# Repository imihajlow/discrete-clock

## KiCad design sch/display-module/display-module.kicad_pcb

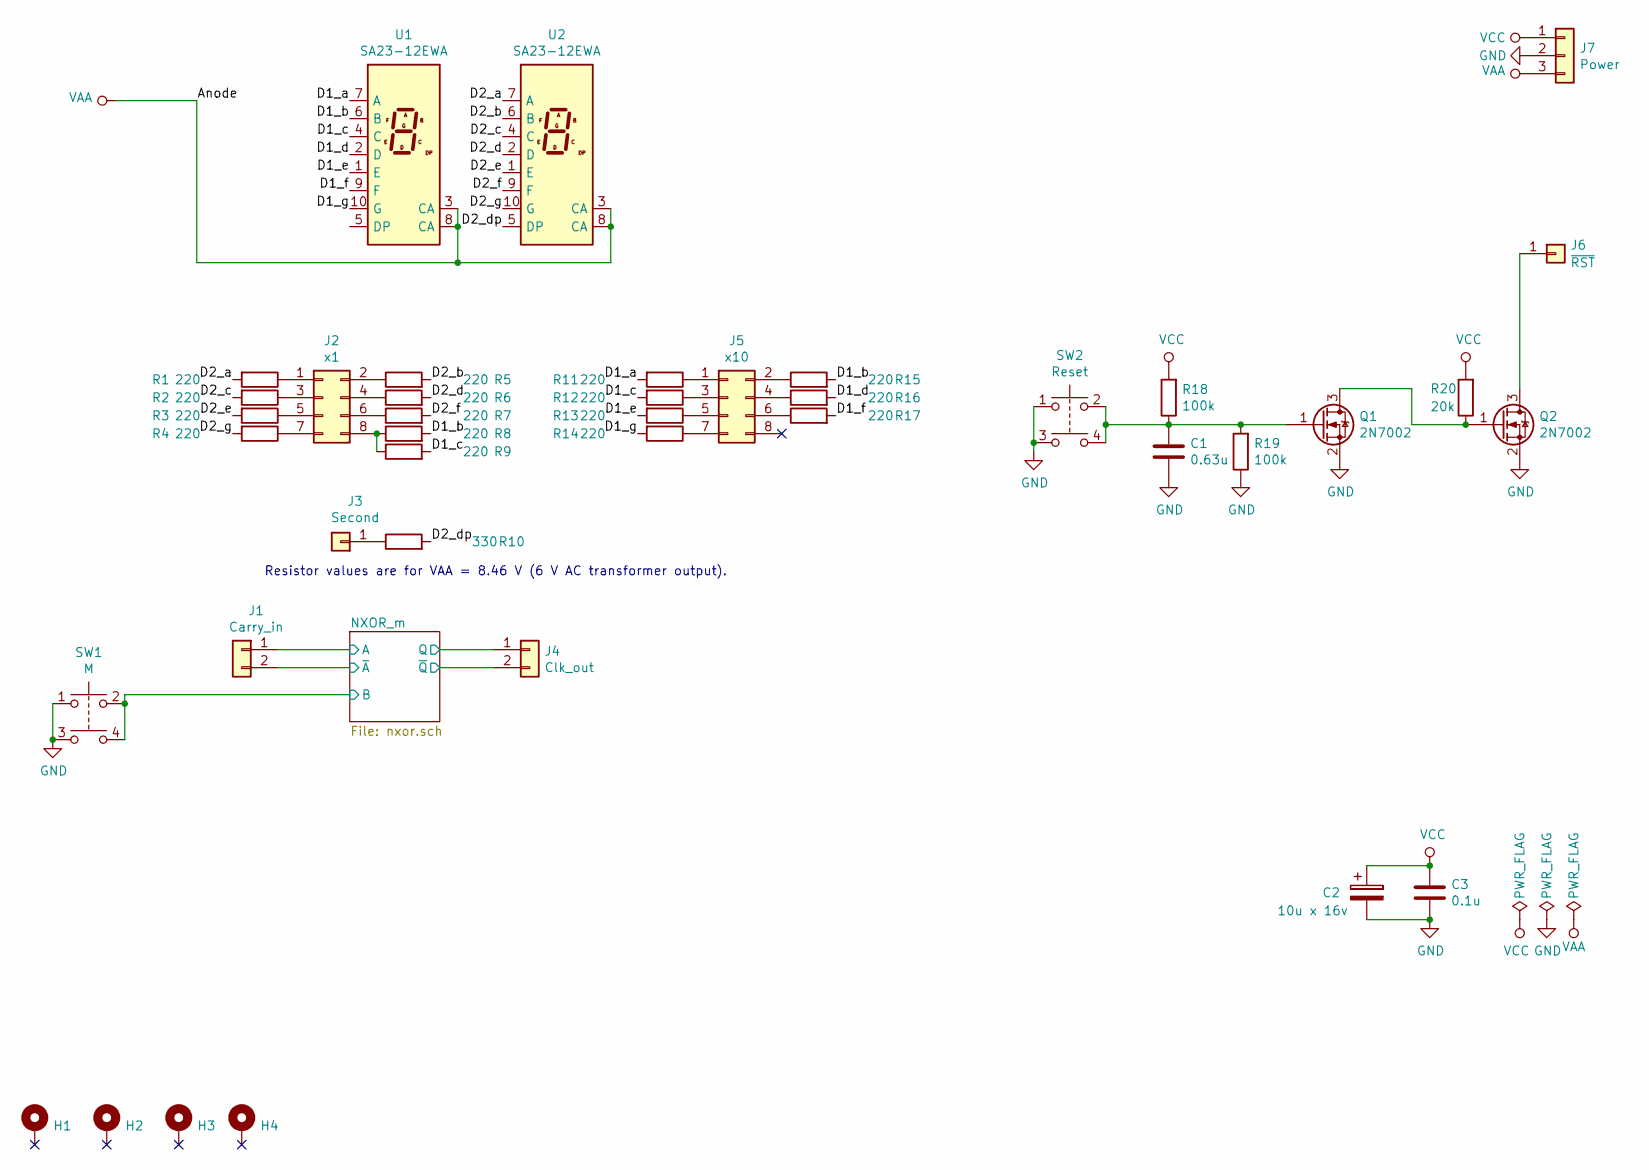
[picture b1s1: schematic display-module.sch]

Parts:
C1: 0.63u; C_0805_2012Metric
C2: 10u x 16v; CP_EIA-3528-21_Kemet-B_Pad1.50x2.35mm_HandSolder
C3: 0.1u; C_0805_2012Metric
H1, H2, H3, H4: MountingHole_Pad; MountingHole_3.2mm_M3_DIN965_Pad
J1: Carry_in; PinHeader_1x02_P2.54mm_Vertical
J2: x1; IDC-Header_2x04_P2.54mm_Vertical
J3: Second; PinHeader_1x01_P2.54mm_Vertical
J4: Clk_out; PinHeader_1x02_P2.54mm_Vertical
J5: x10; IDC-Header_2x04_P2.54mm_Vertical
J6: ~RST; PinHeader_1x01_P2.54mm_Vertical
J7: Power; PinHeader_1x03_P2.54mm_Vertical
Q1, Q2: 2N7002; SOT-23
R1, R2, R3, R4, R5, R6, R7, R8, R9, R11, R12, R13, R14, R15, R16, R17: 220; R_0805_2012Metric
R10: 330; R_0805_2012Metric
R18, R19: 100k; R_0805_2012Metric
R20: 20k; R_0805_2012Metric
SW1: M; DTS-644
SW2: Reset; DTS-644
U1, U2: SA23-12EWA; SA10-21HWA

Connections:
/D1_a: R11.2, U1.7 (A)
/D1_b: R8.2, R15.2, U1.6 (B)
/D1_c: R9.2, R12.2, U1.4 (C)
/D1_d: R16.2, U1.2 (D)
/D1_e: R13.2, U1.1 (E)
/D1_f: R17.2, U1.9 (F)
/D1_g: R14.2, U1.10 (G)
/D2_a: R1.2, U2.7 (A)
/D2_b: R5.2, U2.6 (B)
/D2_c: R2.2, U2.4 (C)
/D2_d: R6.2, U2.2 (D)
/D2_dp: R10.2, U2.5 (DP)
/D2_e: R3.2, U2.1 (E)
/D2_f: R7.2, U2.9 (F)
/D2_g: R4.2, U2.10 (G)
/NXOR_m/A: J1.1; also elsewhere on the board
/NXOR_m/B: SW1.2, SW1.4; also elsewhere on the board
/NXOR_m/Q: J4.1; also elsewhere on the board
/NXOR_m/~A: J1.2; also elsewhere on the board
/NXOR_m/~Q: J4.2; also elsewhere on the board
GND: C1.2, C2.2, C3.2, J7.2, Q1.2 (S), Q2.2 (S), R19.1, SW1.1, SW1.3, SW2.1, SW2.3; also elsewhere on the board
unnamed: C1.1, Q1.1 (G), R18.1, R19.2, SW2.2, SW2.4
unnamed: J2.1, R1.1
unnamed: J2.2, R5.1
unnamed: J2.3, R2.1
unnamed: J2.4, R6.1
unnamed: J2.5, R3.1
unnamed: J2.6, R7.1
unnamed: J2.7, R4.1
unnamed: J2.8, R8.1, R9.1
unnamed: J3.1, R10.1
unnamed: J5.1, R11.1
unnamed: J5.2, R15.1
unnamed: J5.3, R12.1
unnamed: J5.4, R16.1
unnamed: J5.5, R13.1
unnamed: J5.6, R17.1
unnamed: J5.7, R14.1
unnamed: J6.1, Q2.3 (D)
unnamed: Q1.3 (D), Q2.1 (G), R20.1
VAA: J7.3, U1.3 (CA), U1.8 (CA), U2.3 (CA), U2.8 (CA)
VCC: C2.1, C3.1, J7.1, R18.2, R20.2; also elsewhere on the board

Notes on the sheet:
Resistor values are for VAA = 8.46 V (6 V AC transformer output).

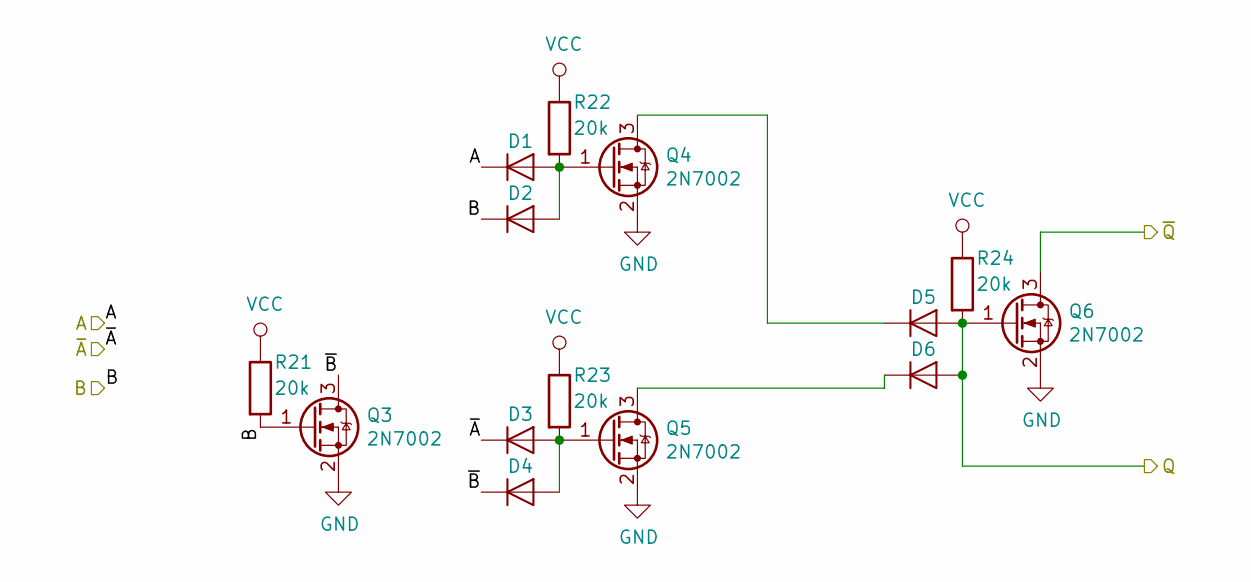
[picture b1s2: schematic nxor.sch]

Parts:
D1, D2, D3, D4, D5, D6: LL103C; D_MiniMELF
Q3, Q4, Q5, Q6: 2N7002; SOT-23
R21, R22, R23, R24: 20k; R_0805_2012Metric

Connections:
/NXOR_m/A: D1.1 (K); also elsewhere on the board
/NXOR_m/B: D2.1 (K), Q3.1 (G), R21.2; also elsewhere on the board
/NXOR_m/Q: D5.2 (A), D6.2 (A), Q6.1 (G), R24.2; also elsewhere on the board
/NXOR_m/~A: D3.1 (K); also elsewhere on the board
/NXOR_m/~B: D4.1 (K), Q3.3 (D)
/NXOR_m/~Q: Q6.3 (D); also elsewhere on the board
GND: Q3.2 (S), Q4.2 (S), Q5.2 (S), Q6.2 (S); also elsewhere on the board
unnamed: D1.2 (A), D2.2 (A), Q4.1 (G), R22.2
unnamed: D3.2 (A), D4.2 (A), Q5.1 (G), R23.2
unnamed: D5.1 (K), Q4.3 (D)
unnamed: D6.1 (K), Q5.3 (D)
VCC: R21.1, R22.1, R23.1, R24.1; also elsewhere on the board

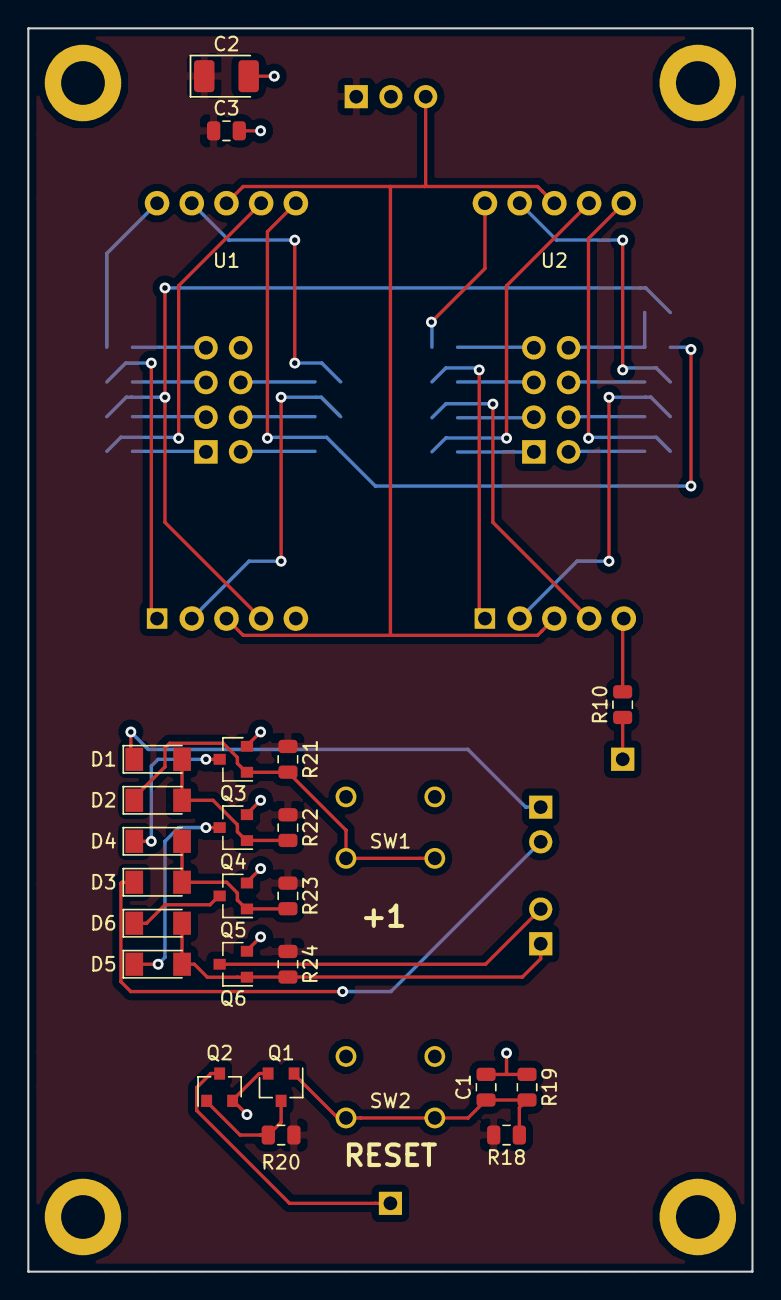
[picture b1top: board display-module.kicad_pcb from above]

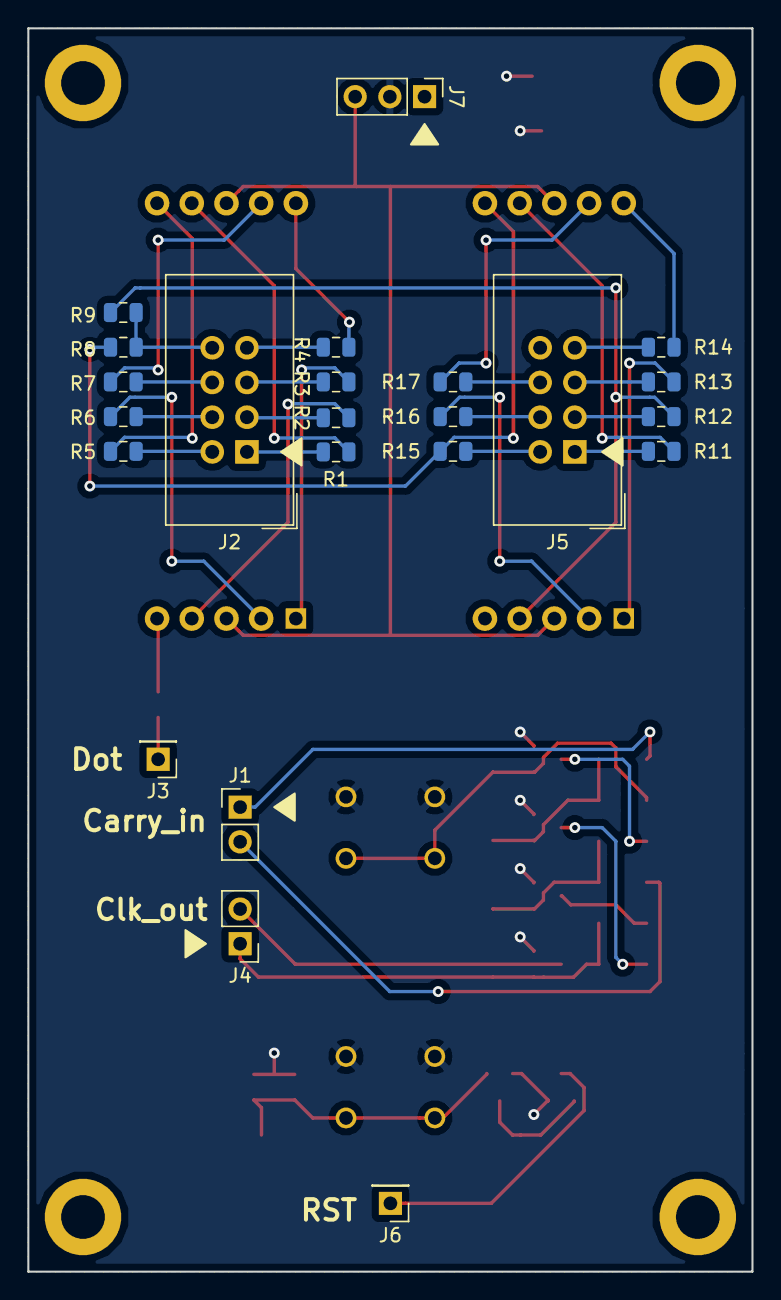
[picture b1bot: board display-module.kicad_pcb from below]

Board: 2 copper layers, 53.0 x 91.0 mm, 54 parts (23 on the bottom side), 47 nets.

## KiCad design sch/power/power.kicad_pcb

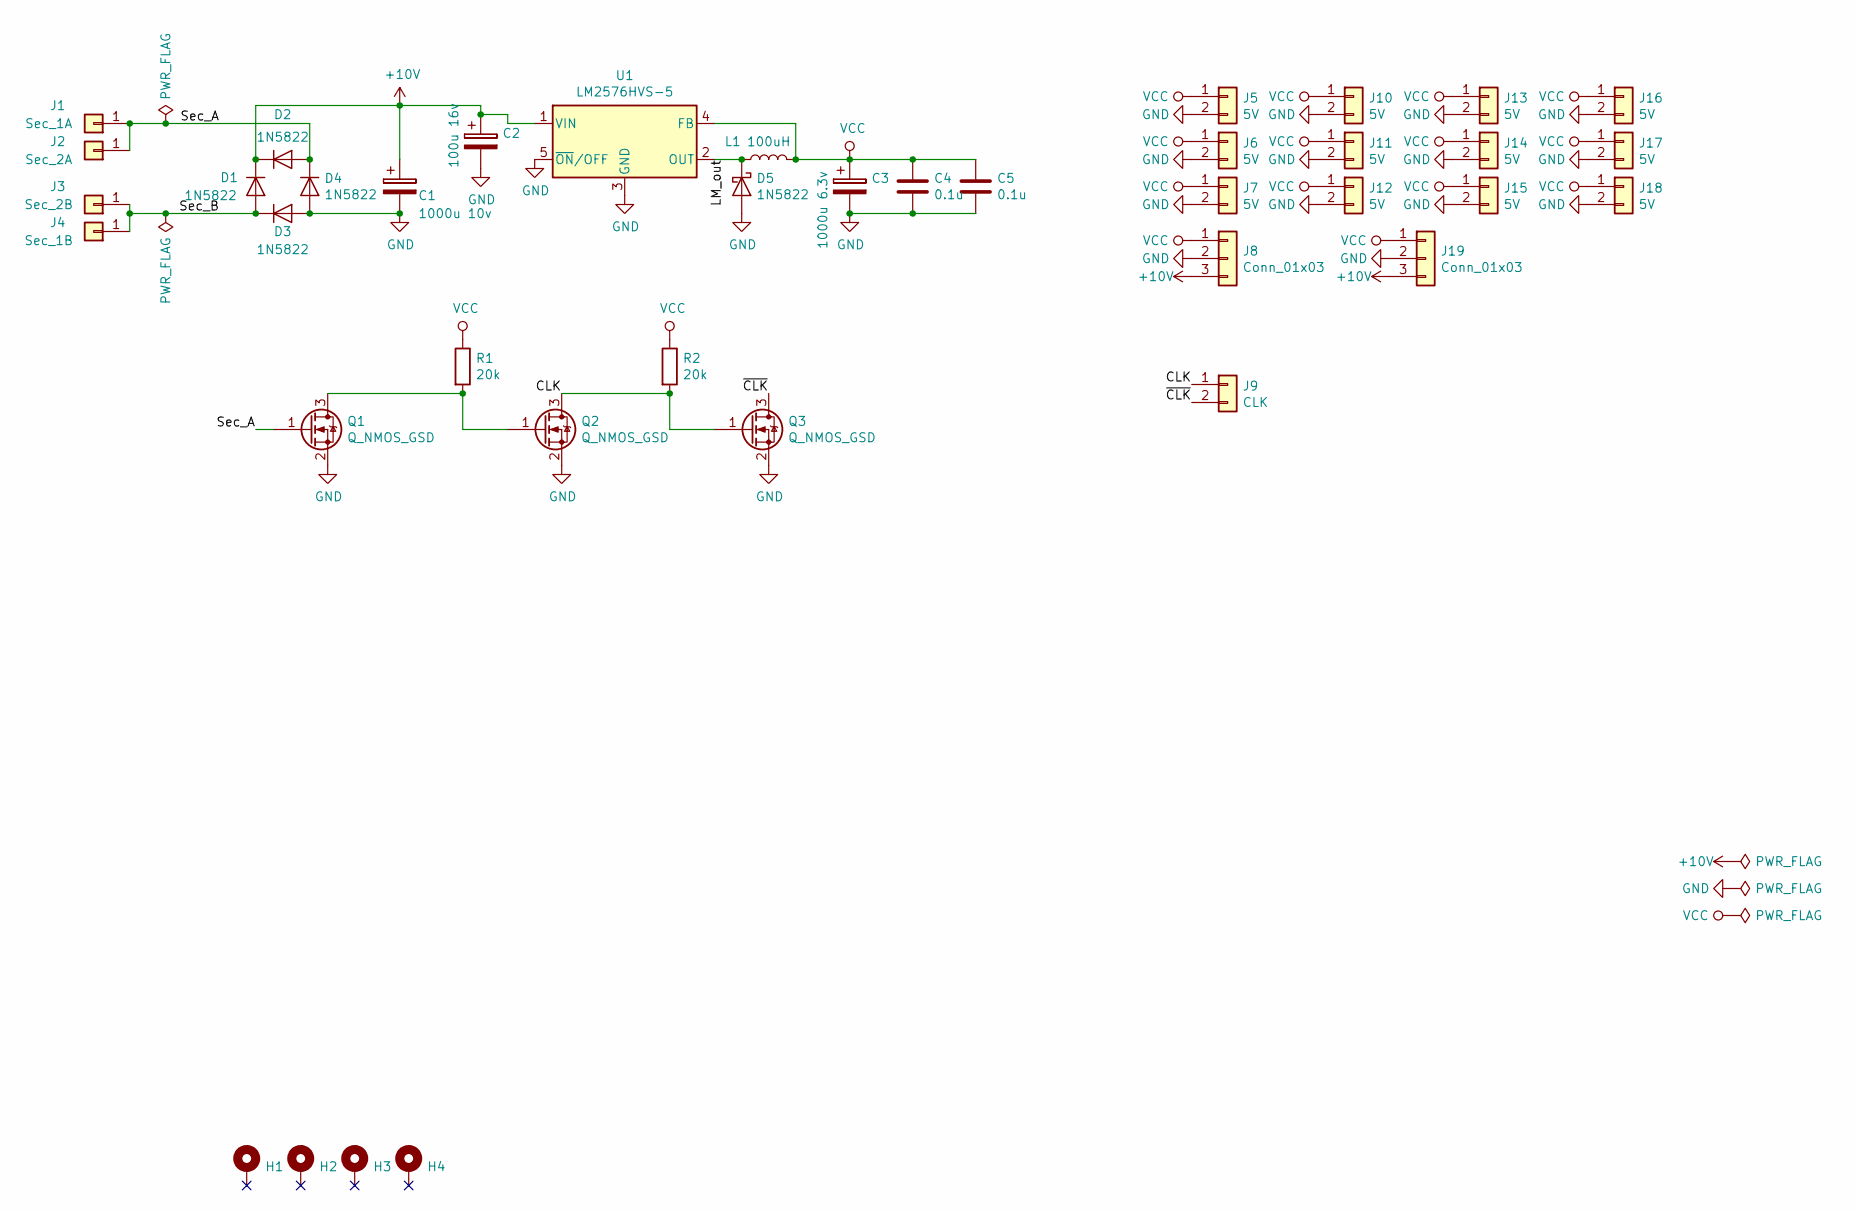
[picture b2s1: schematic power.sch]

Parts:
C1: 1000u 10v; CP_Elec_10x10
C2: 100u 16v; CP_Elec_6.3x5.4
C3: 1000u 6.3v; CP_Elec_8x10.5
C4, C5: 0.1u; C_0805_2012Metric
D1, D2, D3, D4, D5: 1N5822; D_DO-201AD_P12.70mm_Horizontal
H1, H2, H3, H4: MountingHole_Pad; MountingHole_3.2mm_M3_DIN965_Pad
J1: Sec_1A; SolderWirePad_1x01_Drill1.5mm
J2: Sec_2A; SolderWirePad_1x01_Drill1.5mm
J3: Sec_2B; SolderWirePad_1x01_Drill1.5mm
J4: Sec_1B; SolderWirePad_1x01_Drill1.5mm
J5, J6, J7, J10, J11, J12, J13, J14, J15, J16, J17, J18: 5V; PinHeader_1x02_P2.54mm_Vertical
J8, J19: Conn_01x03; PinHeader_1x03_P2.54mm_Vertical
J9: CLK; PinHeader_1x02_P2.54mm_Vertical
L1: 100uH; L_Wuerth_WE-PD-Typ-LS_Handsoldering
Q1, Q2, Q3: Q_NMOS_GSD; SOT-23
R1, R2: 20k; R_0805_2012Metric
U1: LM2576HVS-5; TO-263-5_TabPin3

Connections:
+10V: C1.1, C2.1, D1.1 (K), D2.1 (K), J8.3, J19.3, U1.1 (VIN)
/CLK: J9.1, Q2.3 (D), Q3.1 (G), R2.2
/LM_out: D5.1 (K), L1.1, U1.2 (OUT)
/Sec_A: D2.2 (A), D4.1 (K), J1.1, J2.1, Q1.1 (G)
/Sec_B: D1.2 (A), D3.1 (K), J3.1, J4.1
/~CLK: J9.2, Q3.3 (D)
GND: C1.2, C2.2, C3.2, C4.2, C5.2, D3.2 (A), D4.2 (A), D5.2 (A), J5.2, J6.2, J7.2, J8.2, J10.2, J11.2, J12.2, J13.2, J14.2, J15.2, J16.2, J17.2, J18.2, J19.2, Q1.2 (S), Q2.2 (S), Q3.2 (S), U1.3 (GND), U1.5 (~ON~/OFF)
unnamed: Q1.3 (D), Q2.1 (G), R1.2
VCC: C3.1, C4.1, C5.1, J5.1, J6.1, J7.1, J8.1, J10.1, J11.1, J12.1, J13.1, J14.1, J15.1, J16.1, J17.1, J18.1, J19.1, L1.2, R1.1, R2.1, U1.4 (FB)

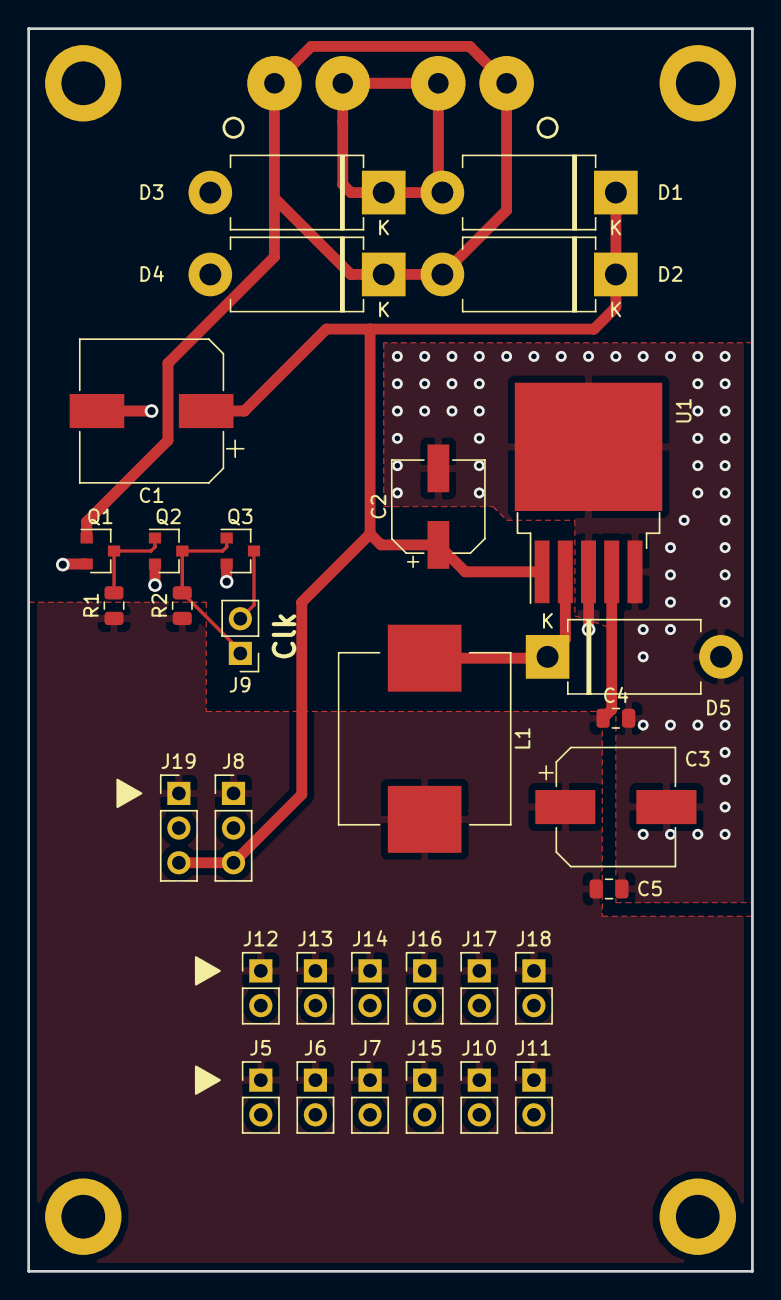
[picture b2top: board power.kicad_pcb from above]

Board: 2 copper layers, 53.0 x 91.0 mm, 40 parts (0 on the bottom side), 9 nets.

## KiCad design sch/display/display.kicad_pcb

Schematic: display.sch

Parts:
C1: 0.63u; C_0805_2012Metric
C2: 10u x 16v; CP_EIA-3528-21_Kemet-B_Pad1.50x2.35mm_HandSolder
C3: 0.1u; C_0805_2012Metric
H1, H2, H3, H4, H5, H6, H7, H8: MountingHole_Pad; MountingHole_3.2mm_M3_DIN965_Pad
J1: S_Carry; PinHeader_1x02_P2.54mm_Vertical
J2: M_Carry; PinHeader_1x02_P2.54mm_Vertical
J3: Hour; IDC-Header_2x04_P2.54mm_Vertical
J4: Second; PinHeader_1x01_P2.54mm_Vertical
J5: M_CLK; PinHeader_1x02_P2.54mm_Vertical
J6: H_CLK; PinHeader_1x02_P2.54mm_Vertical
J7: Minute10; IDC-Header_2x04_P2.54mm_Vertical
J8: Minute1; IDC-Header_2x04_P2.54mm_Vertical
J9: ~RST; PinHeader_1x01_P2.54mm_Vertical
J10: Power; PinHeader_1x03_P2.54mm_Vertical
Q1, Q2: 2N7002; SOT-23
R1, R2, R3, R4, R5, R6, R7, R8, R9, R11, R12, R13, R14, R15, R16, R17, R18, R19, R20, R21, R22, R23, R24: 15; R_0805_2012Metric
R10: 270; R_0805_2012Metric
R25, R26: 100k; R_0805_2012Metric
R27: 20k; R_0805_2012Metric
SW1: M; DTS-644
SW2: H; DTS-644
SW3: Reset; DTS-644
U1, U2, U3, U4: SA23-12EWA; SA10-21HWA

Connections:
/D1_b: R8.2, U1.6 (B)
/D1_c: R9.2, U1.4 (C)
/D2_a: R1.2, U2.7 (A)
/D2_b: R5.2, U2.6 (B)
/D2_c: R2.2, U2.4 (C)
/D2_d: R6.2, U2.2 (D)
/D2_dp: R10.2, U2.5 (DP)
/D2_e: R3.2, U2.1 (E)
/D2_f: R7.2, U2.9 (F)
/D2_g: R4.2, U2.10 (G)
/D3_a: R11.2, U3.7 (A)
/D3_b: R19.2, U3.6 (B)
/D3_c: R12.2, U3.4 (C)
/D3_d: R20.2, U3.2 (D)
/D3_e: R13.2, U3.1 (E)
/D3_f: R21.2, U3.9 (F)
/D3_g: R14.2, U3.10 (G)
/D4_a: R15.2, U4.7 (A)
/D4_b: R22.2, U4.6 (B)
/D4_c: R16.2, U4.4 (C)
/D4_d: R23.2, U4.2 (D)
/D4_e: R17.2, U4.1 (E)
/D4_f: R24.2, U4.9 (F)
/D4_g: R18.2, U4.10 (G)
/NXOR_h/A: J2.1; also elsewhere on the board
/NXOR_h/B: SW2.2, SW2.4; also elsewhere on the board
/NXOR_h/Q: J6.1; also elsewhere on the board
/NXOR_h/~A: J2.2; also elsewhere on the board
/NXOR_h/~Q: J6.2; also elsewhere on the board
/NXOR_m/A: J1.1; also elsewhere on the board
/NXOR_m/B: SW1.2, SW1.4; also elsewhere on the board
/NXOR_m/Q: J5.1; also elsewhere on the board
/NXOR_m/~A: J1.2; also elsewhere on the board
/NXOR_m/~Q: J5.2; also elsewhere on the board
GND: C1.2, C2.2, C3.2, J10.2, Q1.2 (S), Q2.2 (S), R26.1, SW1.1, SW1.3, SW2.1, SW2.3, SW3.1, SW3.3; also elsewhere on the board
unnamed: C1.1, Q1.1 (G), R25.1, R26.2, SW3.2, SW3.4
unnamed: J3.1, R1.1
unnamed: J3.2, R5.1
unnamed: J3.3, R2.1
unnamed: J3.4, R6.1
unnamed: J3.5, R3.1
unnamed: J3.6, R7.1
unnamed: J3.7, R4.1
unnamed: J3.8, R8.1, R9.1
unnamed: J4.1, R10.1
unnamed: J7.1, R11.1
unnamed: J7.2, R19.1
unnamed: J7.3, R12.1
unnamed: J7.4, R20.1
unnamed: J7.5, R13.1
unnamed: J7.6, R21.1
unnamed: J7.7, R14.1
unnamed: J8.1, R15.1
unnamed: J8.2, R22.1
unnamed: J8.3, R16.1
unnamed: J8.4, R23.1
unnamed: J8.5, R17.1
unnamed: J8.6, R24.1
unnamed: J8.7, R18.1
unnamed: J9.1, Q2.3 (D)
unnamed: Q1.3 (D), Q2.1 (G), R27.1
VAA: J10.3, U1.3 (CA), U1.8 (CA), U2.3 (CA), U2.8 (CA), U3.3 (CA), U3.8 (CA), U4.3 (CA), U4.8 (CA)
VCC: C2.1, C3.1, J10.1, R25.2, R27.2; also elsewhere on the board

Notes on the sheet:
Resistor values are for VAA = 8.46 V (6 V AC transformer output).

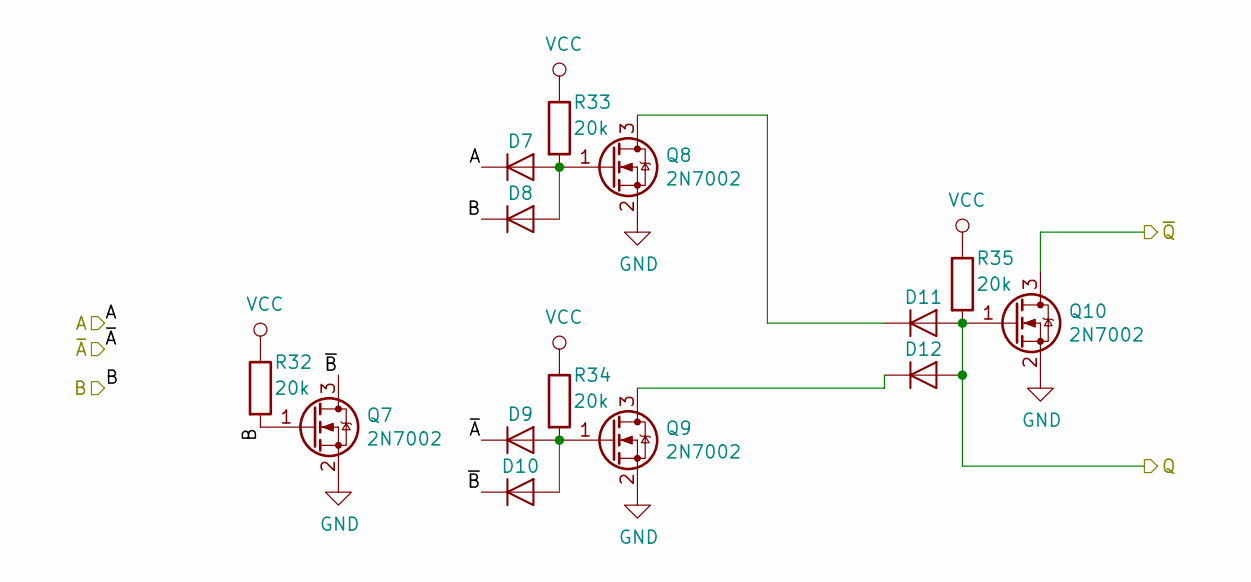
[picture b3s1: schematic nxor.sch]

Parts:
D1, D2, D3, D4, D5, D6: LL103C; D_MiniMELF
Q3, Q4, Q5, Q6: 2N7002; SOT-23
R28, R29, R30, R31: 20k; R_0805_2012Metric

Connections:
/NXOR_m/A: D1.1 (K); also elsewhere on the board
/NXOR_m/B: D2.1 (K), Q3.1 (G), R28.2; also elsewhere on the board
/NXOR_m/Q: D5.2 (A), D6.2 (A), Q6.1 (G), R31.2; also elsewhere on the board
/NXOR_m/~A: D3.1 (K); also elsewhere on the board
/NXOR_m/~B: D4.1 (K), Q3.3 (D)
/NXOR_m/~Q: Q6.3 (D); also elsewhere on the board
GND: Q3.2 (S), Q4.2 (S), Q5.2 (S), Q6.2 (S); also elsewhere on the board
unnamed: D1.2 (A), D2.2 (A), Q4.1 (G), R29.2
unnamed: D3.2 (A), D4.2 (A), Q5.1 (G), R30.2
unnamed: D5.1 (K), Q4.3 (D)
unnamed: D6.1 (K), Q5.3 (D)
VCC: R28.1, R29.1, R30.1, R31.1; also elsewhere on the board

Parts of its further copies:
D7, D8, D9, D10, D11, D12: LL103C; D_MiniMELF
Q7, Q8, Q9, Q10: 2N7002; SOT-23
R32, R33, R34, R35: 20k; R_0805_2012Metric

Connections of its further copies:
/NXOR_h/A: D7.1 (K); also elsewhere on the board
/NXOR_h/B: D8.1 (K), Q7.1 (G), R32.2; also elsewhere on the board
/NXOR_h/Q: D11.2 (A), D12.2 (A), Q10.1 (G), R35.2; also elsewhere on the board
/NXOR_h/~A: D9.1 (K); also elsewhere on the board
/NXOR_h/~B: D10.1 (K), Q7.3 (D)
/NXOR_h/~Q: Q10.3 (D); also elsewhere on the board
GND: Q7.2 (S), Q8.2 (S), Q9.2 (S), Q10.2 (S); also elsewhere on the board
unnamed: D7.2 (A), D8.2 (A), Q8.1 (G), R33.2
unnamed: D9.2 (A), D10.2 (A), Q9.1 (G), R34.2
unnamed: D11.1 (K), Q8.3 (D)
unnamed: D12.1 (K), Q9.3 (D)
VCC: R32.1, R33.1, R34.1, R35.1; also elsewhere on the board

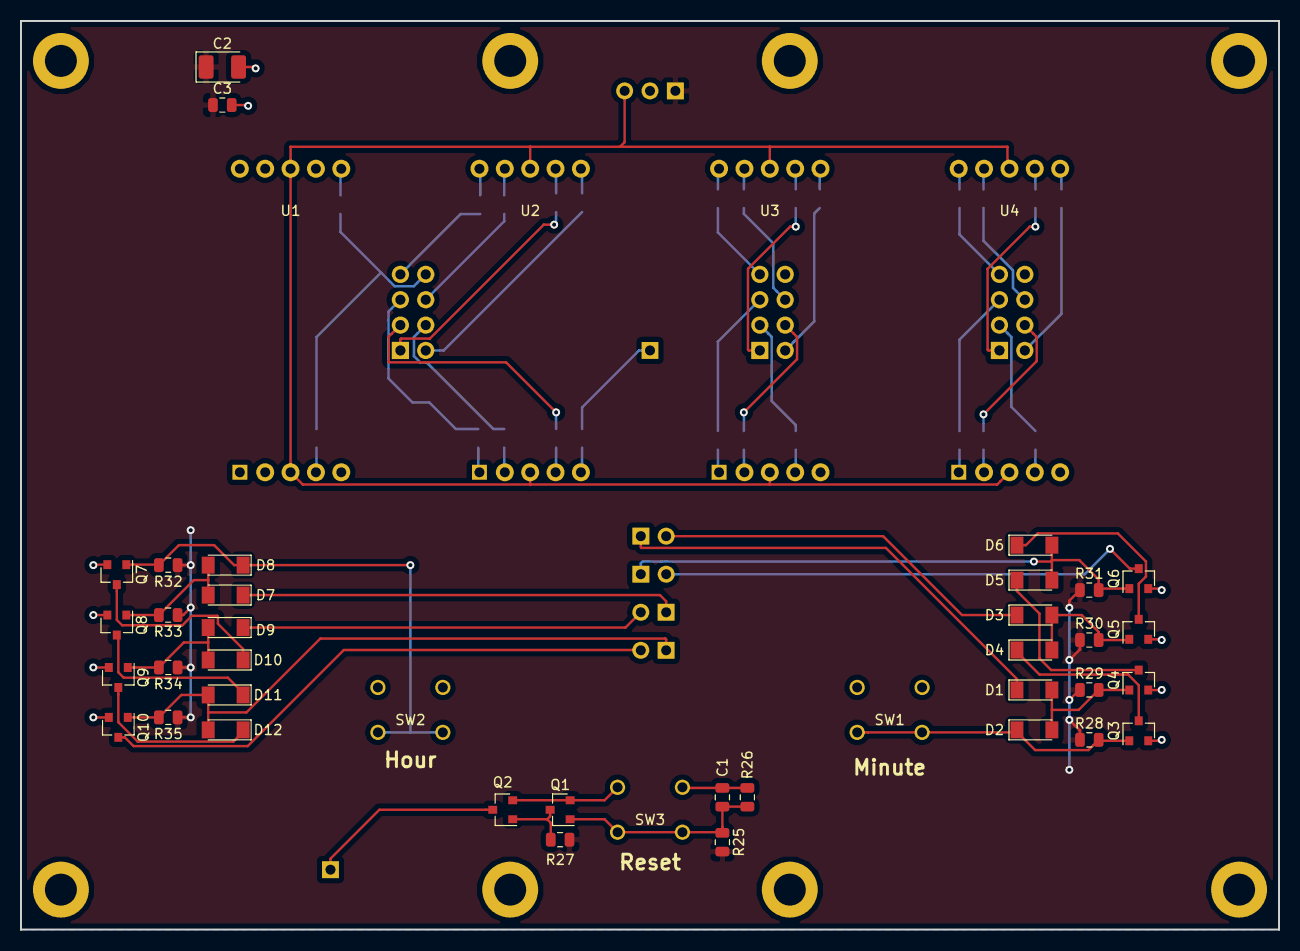
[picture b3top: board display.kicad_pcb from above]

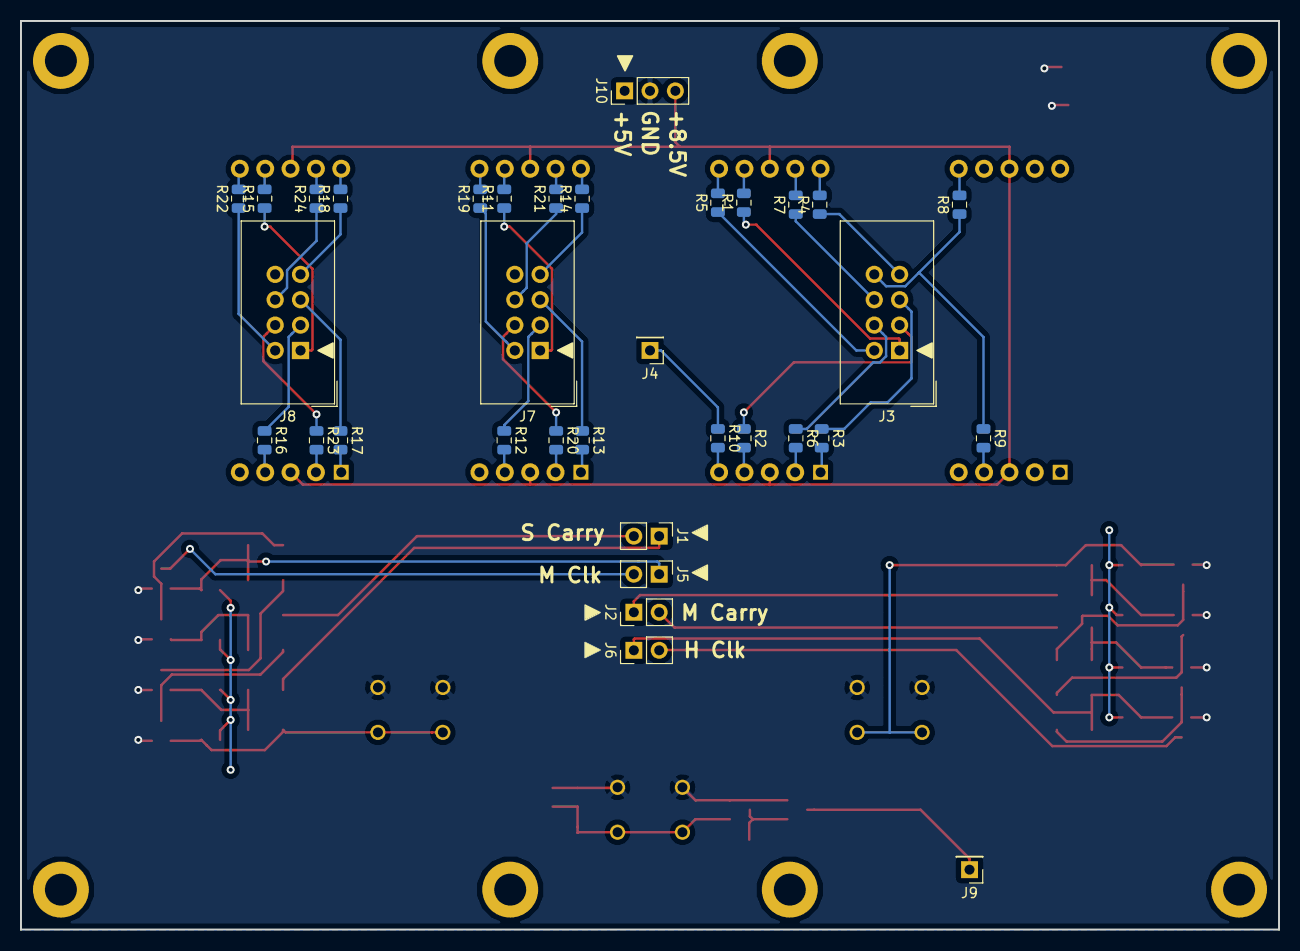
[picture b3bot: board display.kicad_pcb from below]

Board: 2 copper layers, 126.0 x 91.0 mm, 85 parts (34 on the bottom side), 73 nets.

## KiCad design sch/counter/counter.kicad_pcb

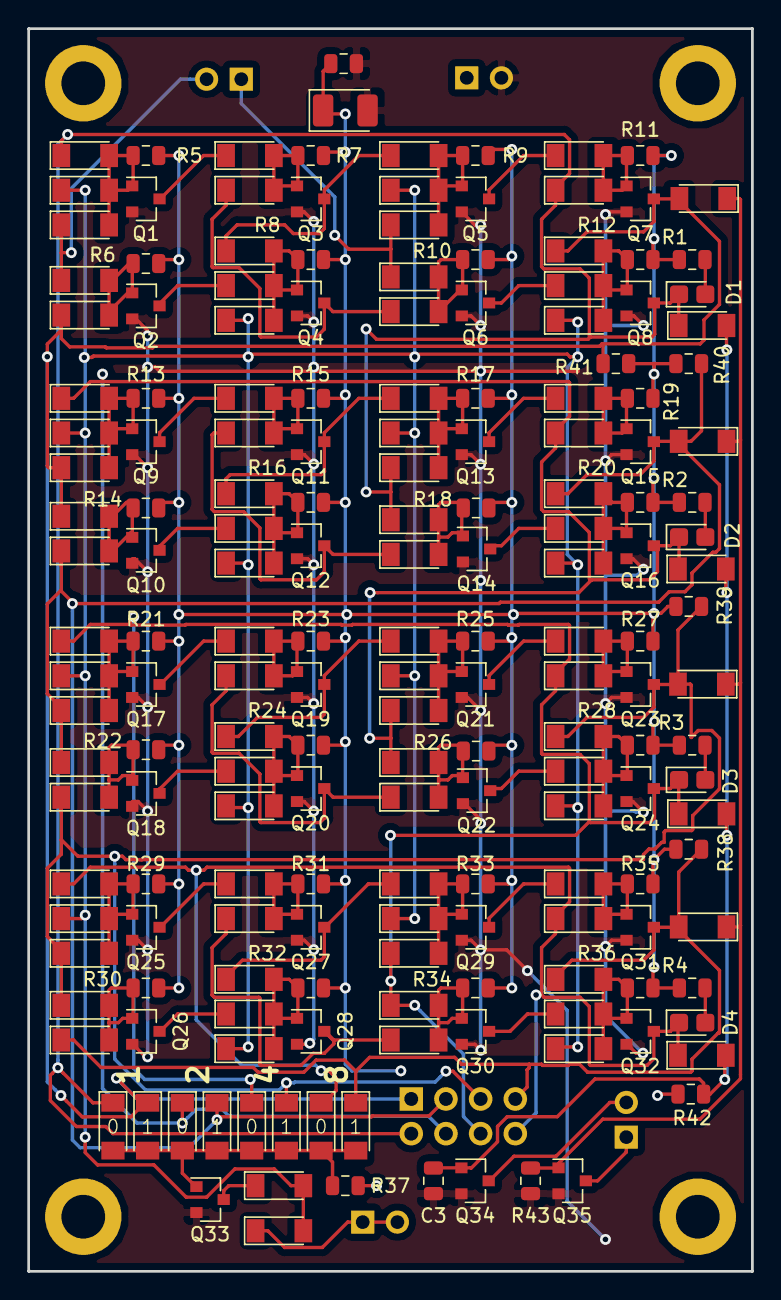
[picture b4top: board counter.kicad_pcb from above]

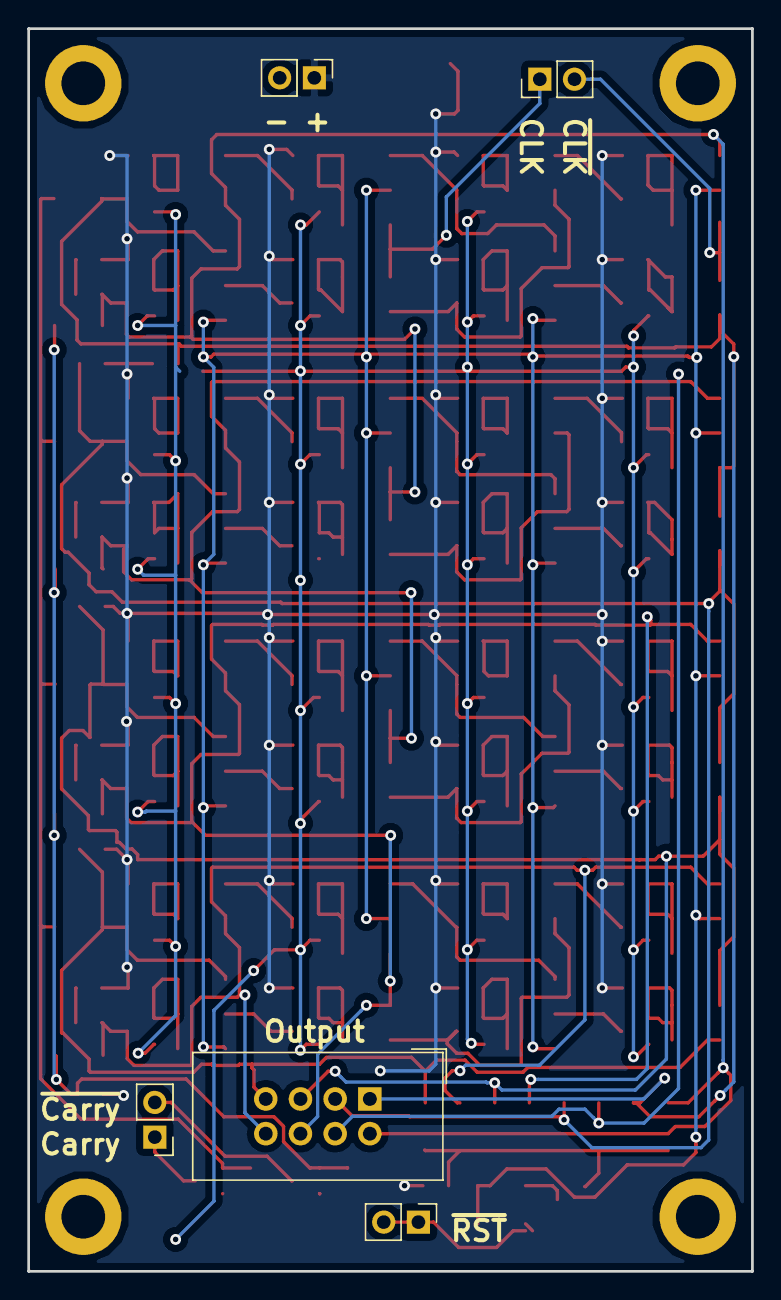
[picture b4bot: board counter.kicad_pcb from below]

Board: 2 copper layers, 53.0 x 91.0 mm, 192 parts (5 on the bottom side), 80 nets.

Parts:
C1: .1u; C_0805_2012Metric
C2: 10u 16v; CP_EIA-3528-21_Kemet-B_Pad1.50x2.35mm_HandSolder
C3: 1n; C_0805_2012Metric
D1, D2, D3, D4: LED; LED_0805_2012Metric_Castellated
D5, D6, D7, D8, D9, D10, D11, D12, D13, D14, D15, D16, D17, D18, D19, D20, D21, D22, D23, D24, D25, D26, D27, D28, D29, D30, D31, D32, D33, D34, D35, D36, D37, D38, D39, D40, D41, D42, D43, D44, D45, D46, D47, D48, D49, D50, D51, D52, D53, D54, D55, D56, D57, D58, D59, D60, D61, D62, D63, D64, D65, D66, D67, D68, D69, D70, D71, D72, D73, D74, D75, D76, D77, D78, D79, D80, D81, D82, D83, D84, D85, D86, D87, D88, D89, D90, D91, D92, D97, D98, D99, D100, D101, D102, D103, D104, D105, D106: D; D_MiniMELF
H1, H2, H3, H4: MountingHole_Pad; MountingHole_3.2mm_M3_DIN965_Pad
J1: CLK; PinHeader_1x02_P2.54mm_Vertical
J2: Carry; PinHeader_1x02_P2.54mm_Vertical
J3: Power; PinHeader_1x02_P2.54mm_Vertical
J4: Q; IDC-Header_2x04_P2.54mm_Vertical
J5: ~RST; PinHeader_1x02_P2.54mm_Vertical
Q1, Q2, Q3, Q4, Q5, Q6, Q7, Q8, Q9, Q10, Q11, Q12, Q13, Q14, Q15, Q16, Q17, Q18, Q19, Q20, Q21, Q22, Q23, Q24, Q25, Q26, Q27, Q28, Q29, Q30, Q31, Q32, Q33, Q34, Q35: Q_NMOS_GSD; SOT-23
R1, R2, R3, R4: 330; R_0805_2012Metric
R5, R6, R7, R8, R9, R10, R11, R12, R13, R14, R15, R16, R17, R18, R19, R20, R21, R22, R23, R24, R25, R26, R27, R28, R29, R30, R31, R32, R33, R34, R35, R36, R37, R42: 20k; R_0805_2012Metric
R38, R39, R40, R41: 10k; R_0805_2012Metric
R43: 40k; R_0805_2012Metric

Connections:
/CLK: D16.1, D19.1, J1.1
/Cout: J2.1, Q35.3
/Q1: D8.1, D22.1, D26.1, D29.1, D85.1, D103.2, J4.1, Q7.3, R41.2
/Q2: D28.1, D42.1, D46.1, D49.1, D87.1, D104.2, J4.3, Q15.3, R40.2
/Q4: D48.1, D62.1, D66.1, D69.1, D89.1, D105.2, J4.5, Q23.3, R39.2
/Q8: D68.1, D82.1, D91.1, D106.2, J4.7, Q31.3, R38.2
/~ARST: D7.1, D14.1, D17.1, D24.1, D27.1, D34.1, D37.1, D44.1, D47.1, D54.1, D57.1, D64.1, D67.1, D74.1, D77.1, D84.1, D97.2, D98.2
/~CLK: D6.1, D9.1, J1.2
/~Cout: J2.2, Q34.3
/~Q1: D1.1, D5.1, D21.1, D36.1, D39.1, D86.1, D99.1, J4.2, Q8.3
/~Q2: D2.1, D25.1, D41.1, D56.1, D59.1, D88.1, D100.1, J4.4, Q16.3
/~Q4: D3.1, D45.1, D61.1, D76.1, D79.1, D90.1, D101.1, J4.6, Q24.3
/~Q8: D4.1, D65.1, D81.1, D92.1, D102.1, J4.8, Q32.3
/~RSTin: D98.1, J5.1, J5.2
GND: C1.2, C2.2, C3.2, J3.2, Q1.2, Q2.2, Q3.2, Q4.2, Q5.2, Q6.2, Q7.2, Q8.2, Q9.2, Q10.2, Q11.2, Q12.2, Q13.2, Q14.2, Q15.2, Q16.2, Q17.2, Q18.2, Q19.2, Q20.2, Q21.2, Q22.2, Q23.2, Q24.2, Q25.2, Q26.2, Q27.2, Q28.2, Q29.2, Q30.2, Q31.2, Q32.2, Q33.2, Q34.2, Q35.2, R43.2
unnamed: C3.1, D99.2, D100.2, D101.2, D102.2, Q34.1, R42.2
unnamed: D1.2, R1.2
unnamed: D2.2, R2.2
unnamed: D3.2, R3.2
unnamed: D4.2, R4.2
unnamed: D5.2, D6.2, D7.2, Q1.1, R5.2
unnamed: D8.2, D9.2, Q2.1, R6.2
unnamed: D10.1, Q1.3
unnamed: D10.2, D11.2, Q3.1, R7.2
unnamed: D11.1, D18.1, Q4.3
unnamed: D12.1, D15.1, Q3.3
unnamed: D12.2, D13.2, D14.2, Q4.1, R8.2
unnamed: D13.1, Q2.3
unnamed: D15.2, D16.2, D17.2, Q5.1, R9.2
unnamed: D18.2, D19.2, Q6.1, R10.2
unnamed: D20.1, Q5.3
unnamed: D20.2, D21.2, Q7.1, R11.2
unnamed: D22.2, D23.2, D24.2, Q8.1, R12.2
unnamed: D23.1, Q6.3
unnamed: D25.2, D26.2, D27.2, Q9.1, R13.2
unnamed: D28.2, D29.2, Q10.1, R14.2
unnamed: D30.1, Q9.3
unnamed: D30.2, D31.2, Q11.1, R15.2
unnamed: D31.1, D38.1, Q12.3
unnamed: D32.1, D35.1, Q11.3
unnamed: D32.2, D33.2, D34.2, Q12.1, R16.2
unnamed: D33.1, Q10.3
unnamed: D35.2, D36.2, D37.2, Q13.1, R17.2
unnamed: D38.2, D39.2, Q14.1, R18.2
unnamed: D40.1, Q13.3
unnamed: D40.2, D41.2, Q15.1, R19.2
unnamed: D42.2, D43.2, D44.2, Q16.1, R20.2
unnamed: D43.1, Q14.3
unnamed: D45.2, D46.2, D47.2, Q17.1, R21.2
unnamed: D48.2, D49.2, Q18.1, R22.2
unnamed: D50.1, Q17.3
unnamed: D50.2, D51.2, Q19.1, R23.2
unnamed: D51.1, D58.1, Q20.3
unnamed: D52.1, D55.1, Q19.3
unnamed: D52.2, D53.2, D54.2, Q20.1, R24.2
unnamed: D53.1, Q18.3
unnamed: D55.2, D56.2, D57.2, Q21.1, R25.2
unnamed: D58.2, D59.2, Q22.1, R26.2
unnamed: D60.1, Q21.3
unnamed: D60.2, D61.2, Q23.1, R27.2
unnamed: D62.2, D63.2, D64.2, Q24.1, R28.2
unnamed: D63.1, Q22.3
unnamed: D65.2, D66.2, D67.2, Q25.1, R29.2
unnamed: D68.2, D69.2, Q26.1, R30.2
unnamed: D70.1, Q25.3
unnamed: D70.2, D71.2, Q27.1, R31.2
unnamed: D71.1, D78.1, Q28.3
unnamed: D72.1, D75.1, Q27.3
unnamed: D72.2, D73.2, D74.2, Q28.1, R32.2
unnamed: D73.1, Q26.3
unnamed: D75.2, D76.2, D77.2, Q29.1, R33.2
unnamed: D78.2, D79.2, Q30.1, R34.2
unnamed: D80.1, Q29.3
unnamed: D80.2, D81.2, Q31.1, R35.2
unnamed: D82.2, D83.2, D84.2, Q32.1, R36.2
unnamed: D83.1, Q30.3
unnamed: D85.2, D86.2, D87.2, D88.2, D89.2, D90.2, D91.2, D92.2, Q33.1, R37.2
unnamed: D97.1, Q33.3
unnamed: D103.1, D104.1, D105.1, D106.1, Q35.1, R43.1
VCC: C1.1, C2.1, J3.1, R1.1, R2.1, R3.1, R4.1, R5.1, R6.1, R7.1, R8.1, R9.1, R10.1, R11.1, R12.1, R13.1, R14.1, R15.1, R16.1, R17.1, R18.1, R19.1, R20.1, R21.1, R22.1, R23.1, R24.1, R25.1, R26.1, R27.1, R28.1, R29.1, R30.1, R31.1, R32.1, R33.1, R34.1, R35.1, R36.1, R37.1, R38.1, R39.1, R40.1, R41.1, R42.1
